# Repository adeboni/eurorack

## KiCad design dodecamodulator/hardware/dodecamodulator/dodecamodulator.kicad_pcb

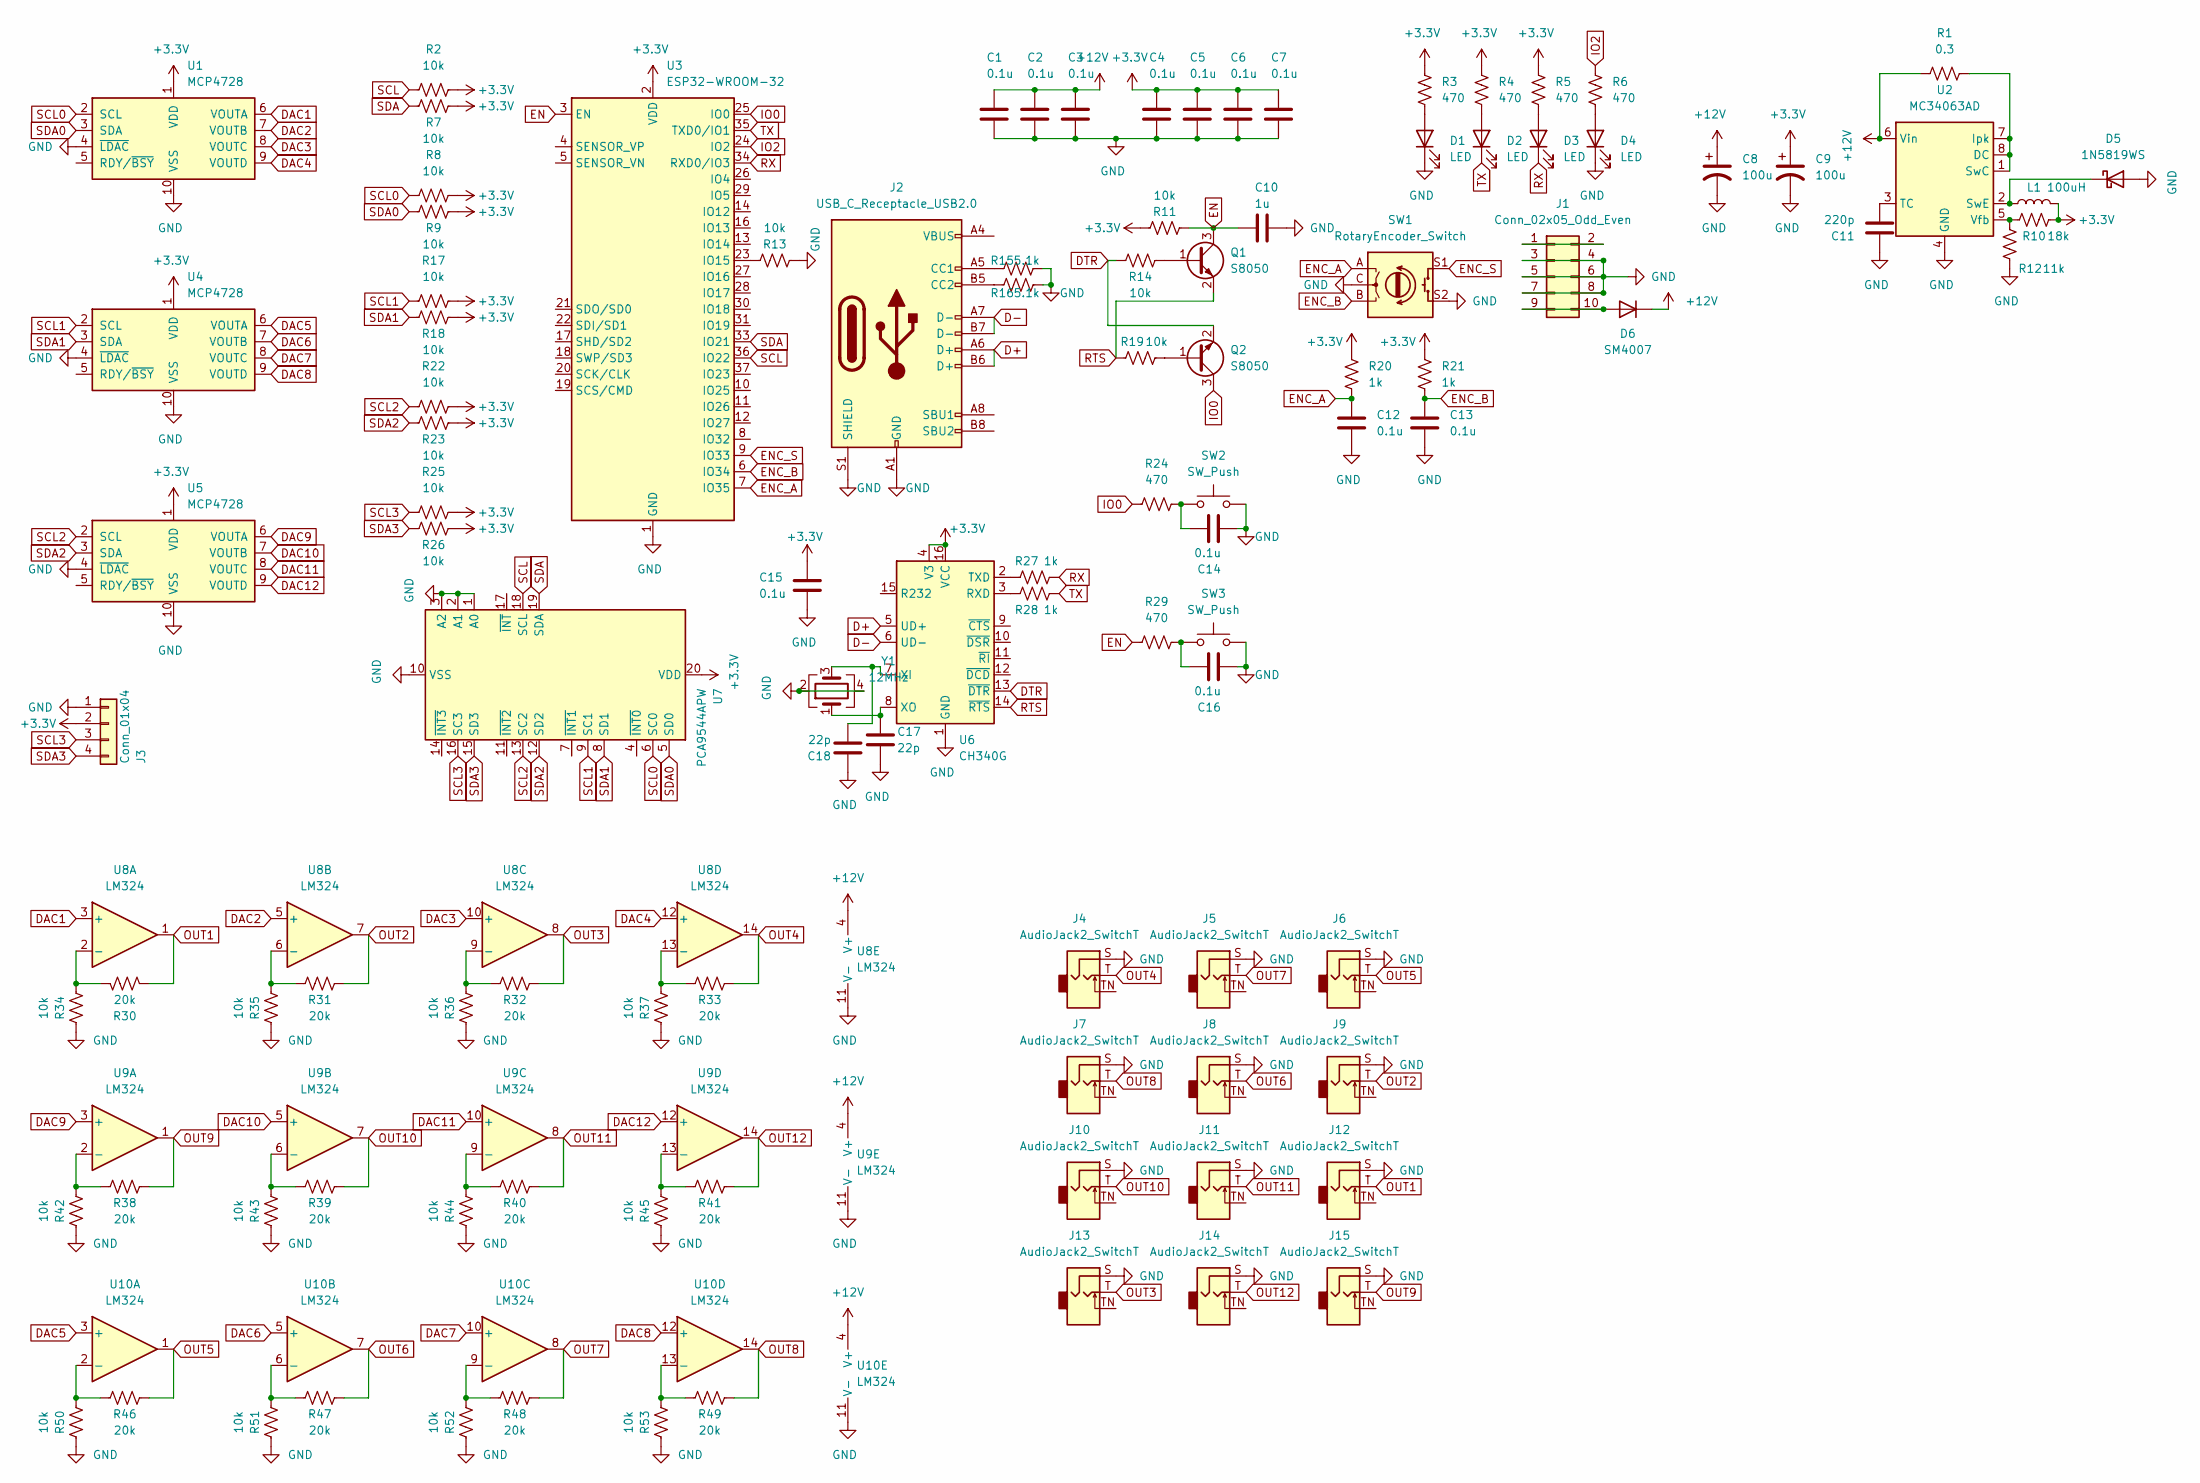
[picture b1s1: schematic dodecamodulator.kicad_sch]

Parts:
C1, C2, C3, C4, C5, C6, C7, C12, C13, C14, C15, C16: 0.1u; C_0603_1608Metric
C8, C9: 100u; CP_Elec_5x5.7
C10: 1u; C_0603_1608Metric
C11: 220p; C_0603_1608Metric
C17, C18: 22p; C_0603_1608Metric
D1, D2, D3, D4: LED; LED_0603_1608Metric
D5: 1N5819WS; D_SOD-323
D6: SM4007; D_SOD-123
J1: Conn_02x05_Odd_Even; IDC-Header_2x05_P2.54mm_Vertical
J2: USB_C_Receptacle_USB2.0; USB_C_Receptacle_Palconn_UTC16-G
J3: Conn_01x04; SSD1106
J4, J5, J6, J7, J8, J9, J10, J11, J12, J13, J14, J15: AudioJack2_SwitchT; Jack_3.5mm_QingPu_WQP-PJ398SM_Vertical_CircularHoles
L1: 100uH; L_7.3x7.3_H3.5
Q1, Q2: S8050; SOT-23
R1: 0.3; R_0603_1608Metric
R2, R7, R8, R9, R11, R13, R14, R17, R18, R19, R22, R23, R25, R26, R34, R35, R36, R37, R42, R43, R44, R45, R50, R51, R52, R53: 10k; R_0603_1608Metric
R3, R4, R5, R6, R24, R29: 470; R_0603_1608Metric
R10: 18k; R_0603_1608Metric
R12: 11k; R_0603_1608Metric
R15, R16: 5.1k; R_0603_1608Metric
R20, R21, R27, R28: 1k; R_0603_1608Metric
R30, R31, R32, R33, R38, R39, R40, R41, R46, R47, R48, R49: 20k; R_0603_1608Metric
SW1: RotaryEncoder_Switch; RotaryEncoder_Alps_EC11E-Switch_Vertical_H20mm
SW2, SW3: SW_Push; SW_SPST_TL3342
U1, U4, U5: MCP4728; MSOP-10_3x3mm_P0.5mm
U2: MC34063AD; SOIC-8_3.9x4.9mm_P1.27mm
U3: ESP32-WROOM-32
U6: CH340G; SOIC-16_3.9x9.9mm_P1.27mm
U7: PCA9544APW; TSSOP-20_4.4x6.5mm_P0.65mm
U8, U9, U10: LM324; SOIC-14_3.9x8.7mm_P1.27mm
Y1: 12MHz; Crystal_SMD_3225-4Pin_3.2x2.5mm

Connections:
+3V3: C4.1, C5.1, C6.1, C7.1, C9.1, C15.1, J3.2, L1.2, R2.2, R3.2, R4.2, R5.2, R7.2, R8.2, R9.2, R10.2, R11.2, R17.2, R18.2, R20.2, R21.2, R22.2, R23.2, R25.2, R26.2, U1.1 (VDD), U3.2 (VDD), U4.1 (VDD), U5.1 (VDD), U6.4 (V3), U6.16 (VCC), U7.20 (VDD)
+12V: C1.1, C2.1, C3.1, C8.1, D6.1 (K), R1.2, U2.6 (Vin), U8.4 (V+), U9.4 (V+), U10.4 (V+)
D+: J2.A6 (D+), J2.B6 (D+), U6.5 (UD+)
D-: J2.A7 (D-), J2.B7 (D-), U6.6 (UD-)
DAC1: U1.6 (VOUTA), U8.3 (+)
DAC2: U1.7 (VOUTB), U8.5 (+)
DAC3: U1.8 (VOUTC), U8.10 (+)
DAC4: U1.9 (VOUTD), U8.12 (+)
DAC5: U4.6 (VOUTA), U10.3 (+)
DAC6: U4.7 (VOUTB), U10.5 (+)
DAC7: U4.8 (VOUTC), U10.10 (+)
DAC8: U4.9 (VOUTD), U10.12 (+)
DAC9: U5.6 (VOUTA), U9.3 (+)
DAC10: U5.7 (VOUTB), U9.5 (+)
DAC11: U5.8 (VOUTC), U9.10 (+)
DAC12: U5.9 (VOUTD), U9.12 (+)
DTR: Q2.2 (E), R14.1, U6.13 (~DTR)
EN: C10.2, Q1.3 (C), R11.1, R29.2, U3.3 (EN)
ENC_A: C12.1, R20.1, SW1.A, U3.7 (IO35)
ENC_B: C13.1, R21.1, SW1.B, U3.6 (IO34)
ENC_S: SW1.S1, U3.9 (IO33)
GND: C1.2, C2.2, C3.2, C4.2, C5.2, C6.2, C7.2, C8.2, C9.2, C10.1, C11.1, C12.2, C13.2, C14.2, C15.2, C16.2, C17.2, C18.1, D1.1 (K), D4.1 (K), D5.2 (A), J1.3, J1.4, J1.5, J1.6, J1.7, J1.8, J2.A1 (GND), J2.A12 (GND), J2.B1 (GND), J2.B12 (GND), J2.S1 (SHIELD), J3.1, J4.S, J5.S, J6.S, J7.S, J8.S, J9.S, J10.S, J11.S, J12.S, J13.S, J14.S, J15.S, R12.2, R13.1, R15.1, R16.1, R34.2, R35.2, R36.2, R37.2, R42.2, R43.2, R44.2, R45.2, R50.2, R51.2, R52.2, R53.2, SW1.C, SW1.S2, SW2.2, SW3.2, U1.4 (~LDAC), U1.10 (VSS), U2.4 (GND), U3.1 (GND), U3.15 (GND), U3.38 (GND), U3.39 (GND), U4.4 (~LDAC), U4.10 (VSS), U5.4 (~LDAC), U5.10 (VSS), U6.1 (GND), U7.1 (A0), U7.2 (A1), U7.3 (A2), U7.10 (VSS), U8.11 (V-), U9.11 (V-), U10.11 (V-), Y1.2, Y1.4
IO0: Q2.3 (C), R24.2, U3.25 (IO0)
IO2: R6.2, U3.24 (IO2)
unnamed: C11.2, U2.3 (TC)
unnamed: C14.1, R24.1, SW2.1
unnamed: C16.1, R29.1, SW3.1
unnamed: C17.1, U6.8 (XO), Y1.1
unnamed: C18.2, U6.7 (XI), Y1.3
unnamed: D1.2 (A), R3.1
unnamed: D2.2 (A), R4.1
unnamed: D3.2 (A), R5.1
unnamed: D4.2 (A), R6.1
unnamed: D5.1 (K), L1.1, U2.2 (SwE)
unnamed: D6.2 (A), J1.9, J1.10
unnamed: J1.1, J1.2
unnamed: J2.A4 (VBUS), J2.A9 (VBUS), J2.B4 (VBUS), J2.B9 (VBUS)
unnamed: J2.A5 (CC1), R15.2
unnamed: J2.B5 (CC2), R16.2
unnamed: Q1.1 (B), R14.2
unnamed: Q2.1 (B), R19.2
unnamed: R1.1, U2.1 (SwC), U2.7 (Ipk), U2.8 (DC)
unnamed: R10.1, R12.1, U2.5 (Vfb)
unnamed: R13.2, U3.23 (IO15)
unnamed: R27.2, U6.2 (TXD)
unnamed: R28.2, U6.3 (RXD)
unnamed: R30.1, R34.1, U8.2 (-)
unnamed: R31.1, R35.1, U8.6 (-)
unnamed: R32.1, R36.1, U8.9 (-)
unnamed: R33.1, R37.1, U8.13 (-)
unnamed: R38.1, R42.1, U9.2 (-)
unnamed: R39.1, R43.1, U9.6 (-)
unnamed: R40.1, R44.1, U9.9 (-)
unnamed: R41.1, R45.1, U9.13 (-)
unnamed: R46.1, R50.1, U10.2 (-)
unnamed: R47.1, R51.1, U10.6 (-)
unnamed: R48.1, R52.1, U10.9 (-)
unnamed: R49.1, R53.1, U10.13 (-)
OUT1: J12.T, R30.2, U8.1
OUT2: J9.T, R31.2, U8.7
OUT3: J13.T, R32.2, U8.8
OUT4: J4.T, R33.2, U8.14
OUT5: J6.T, R46.2, U10.1
OUT6: J8.T, R47.2, U10.7
OUT7: J5.T, R48.2, U10.8
OUT8: J7.T, R49.2, U10.14
OUT9: J15.T, R38.2, U9.1
OUT10: J10.T, R39.2, U9.7
OUT11: J11.T, R40.2, U9.8
OUT12: J14.T, R41.2, U9.14
RTS: Q1.2 (E), R19.1, U6.14 (~RTS)
RX: D3.1 (K), R27.1, U3.34 (RXD0/IO3)
SCL: R2.1, U3.36 (IO22), U7.18 (SCL)
SCL0: R8.1, U1.2 (SCL), U7.6 (SC0)
SCL1: R17.1, U4.2 (SCL), U7.9 (SC1)
SCL2: R22.1, U5.2 (SCL), U7.13 (SC2)
SCL3: J3.3, R25.1, U7.16 (SC3)
SDA: R7.1, U3.33 (IO21), U7.19 (SDA)
SDA0: R9.1, U1.3 (SDA), U7.5 (SD0)
SDA1: R18.1, U4.3 (SDA), U7.8 (SD1)
SDA2: R23.1, U5.3 (SDA), U7.12 (SD2)
SDA3: J3.4, R26.1, U7.15 (SD3)
TX: D2.1 (K), R28.1, U3.35 (TXD0/IO1)

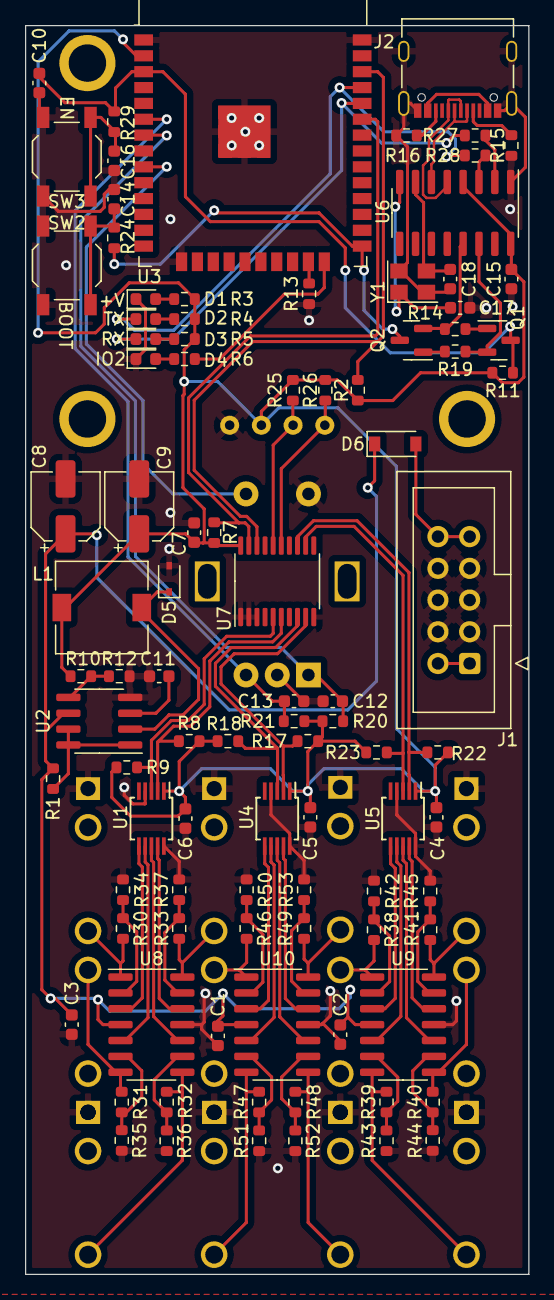
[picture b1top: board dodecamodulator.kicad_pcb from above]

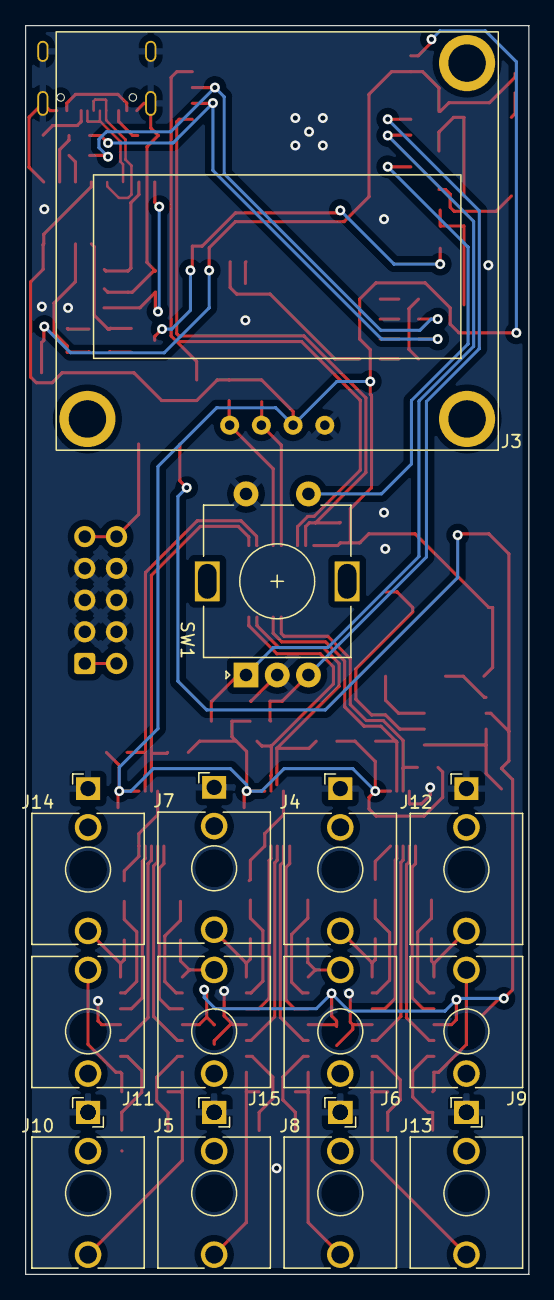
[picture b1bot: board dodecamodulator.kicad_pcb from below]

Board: 2 copper layers, 40.3 x 100.0 mm, 109 parts (14 on the bottom side), 83 nets.

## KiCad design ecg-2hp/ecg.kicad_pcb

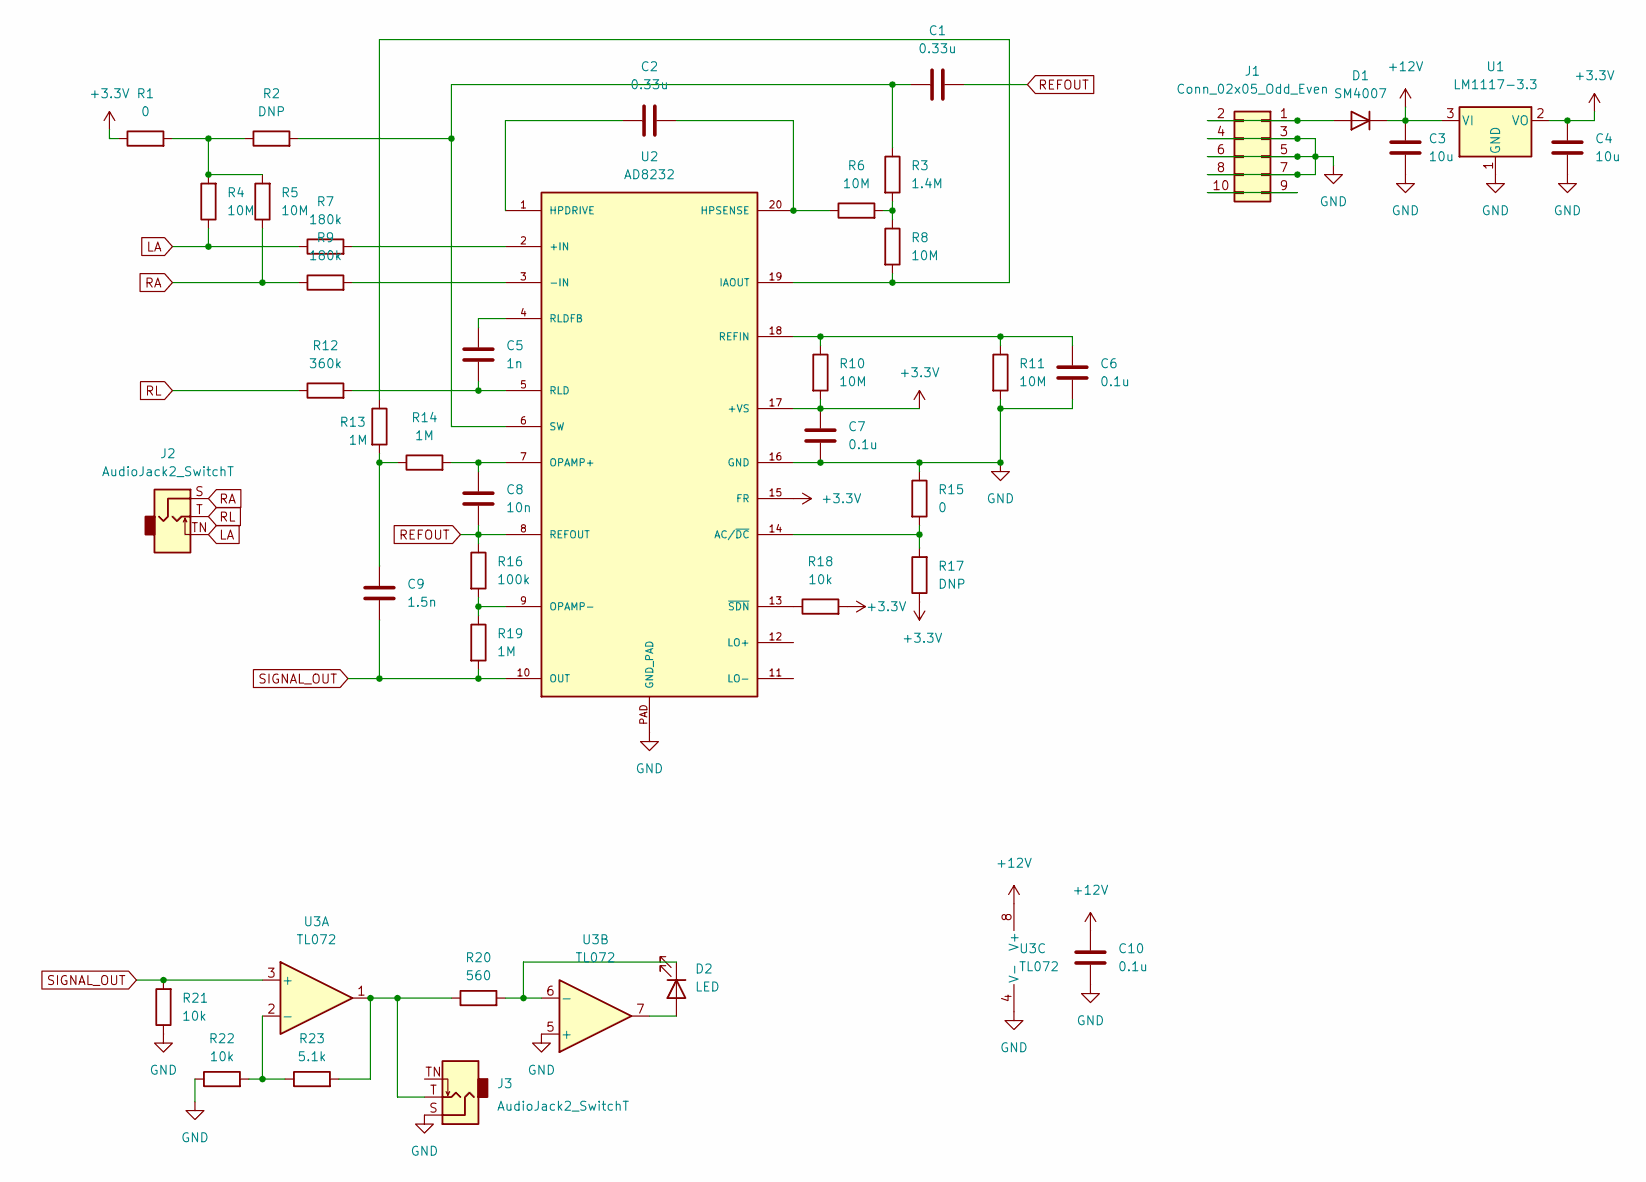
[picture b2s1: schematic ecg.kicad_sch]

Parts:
C1, C2: 0.33u; C_0603_1608Metric
C3, C4: 10u; C_0603_1608Metric
C5: 1n; C_0603_1608Metric
C6, C7, C10: 0.1u; C_0603_1608Metric
C8: 10n; C_0603_1608Metric
C9: 1.5n; C_0603_1608Metric
D1: SM4007; D_SOD-123
D2: LED; LED_D3.0mm_FlatTop
J1: Conn_02x05_Odd_Even; Pins_2x05_2.54mm_TH_Europower
J2, J3: AudioJack2_SwitchT; Jack_3.5mm_QingPu_WQP-PJ398SM_Vertical_CircularHoles
R1, R15: 0; R_0603_1608Metric
R2, R17: DNP; R_0603_1608Metric
R3: 1.4M; R_0603_1608Metric
R4, R5, R6, R8, R10, R11: 10M; R_0603_1608Metric
R7, R9: 180k; R_0603_1608Metric
R12: 360k; R_0603_1608Metric
R13, R14, R19: 1M; R_0603_1608Metric
R16: 100k; R_0603_1608Metric
R18, R21, R22: 10k; R_0603_1608Metric
R20: 560; R_0603_1608Metric
R23: 5.1k; R_0603_1608Metric
U1: LM1117-3.3; SOT-223-3_TabPin2
U2: AD8232; LFCSP_20
U3: TL072; SOIC-8_3.9x4.9mm_P1.27mm

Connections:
+3V3: C4.2, C7.2, R1.1, R10.2, R17.1, R18.2, U1.2 (VO), U2.15 (FR), U2.17 (+VS)
+12V: C3.2, C10.2, D1.1 (K), U1.3 (VI), U3.8 (V+)
GND: C3.1, C4.1, C6.1, C7.1, C10.1, J1.3, J1.4, J1.5, J1.6, J1.7, J1.8, J3.S, R11.2, R15.1, R21.1, R22.1, U1.1 (GND), U2.16 (GND), U2.PAD (GND_PAD), U3.4 (V-), U3.5 (+)
LA: J2.TN, R4.1, R7.1
unnamed: C1.2, R2.2, R3.1, U2.6 (SW)
unnamed: C2.1, R6.1, U2.20 (HPSENSE)
unnamed: C2.2, U2.1 (HPDRIVE)
unnamed: C5.1, R12.2, U2.5 (RLD)
unnamed: C5.2, U2.4 (RLDFB)
unnamed: C6.2, R10.1, R11.1, U2.18 (REFIN)
unnamed: C8.2, R14.2, U2.7 (OPAMP+)
unnamed: C9.2, R13.2, R14.1
unnamed: D1.2 (A), J1.1, J1.2
unnamed: D2.1 (K), R20.2, U3.6 (-)
unnamed: D2.2 (A), U3.7
unnamed: J1.9, J1.10
unnamed: J3.T, R20.1, R23.2, U3.1
unnamed: R1.2, R2.1, R4.2, R5.2
unnamed: R3.2, R6.2, R8.1
unnamed: R7.2, U2.2 (+IN)
unnamed: R9.2, U2.3 (-IN)
unnamed: R8.2, R13.1, U2.19 (IAOUT)
unnamed: R15.2, R17.2, U2.14 (AC/~DC)
unnamed: R16.2, R19.1, U2.9 (OPAMP-)
unnamed: R18.1, U2.13 (~SDN)
unnamed: R22.2, R23.1, U3.2 (-)
RA: J2.S, R5.1, R9.1
REFOUT: C1.1, C8.1, R16.1, U2.8 (REFOUT)
RL: J2.T, R12.1
SIGNAL_OUT: C9.1, R19.2, R21.2, U2.10 (OUT), U3.3 (+)

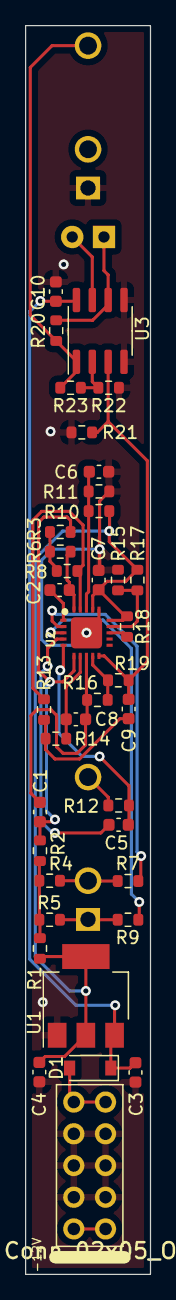
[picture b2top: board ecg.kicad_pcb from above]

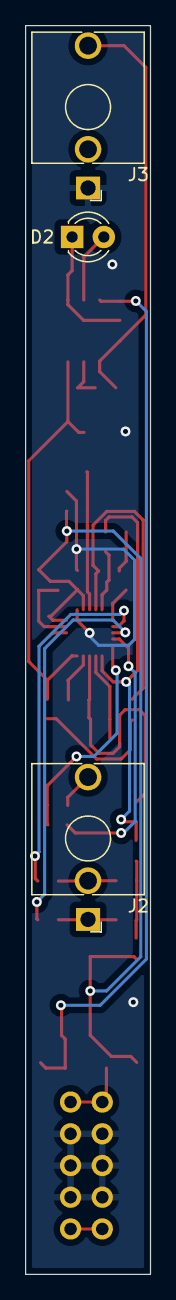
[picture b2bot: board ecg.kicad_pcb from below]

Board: 2 copper layers, 10.0 x 100.0 mm, 41 parts (3 on the bottom side), 30 nets.

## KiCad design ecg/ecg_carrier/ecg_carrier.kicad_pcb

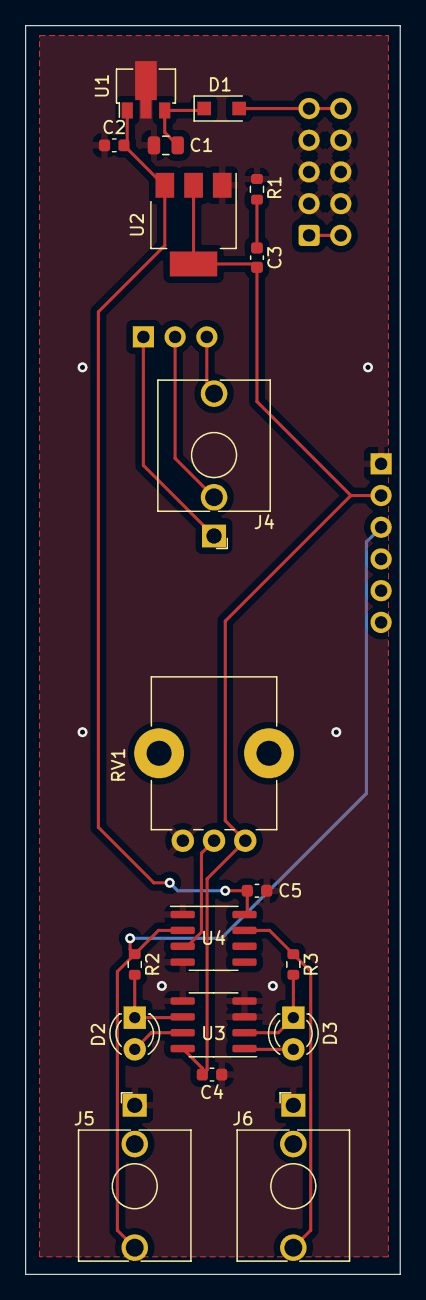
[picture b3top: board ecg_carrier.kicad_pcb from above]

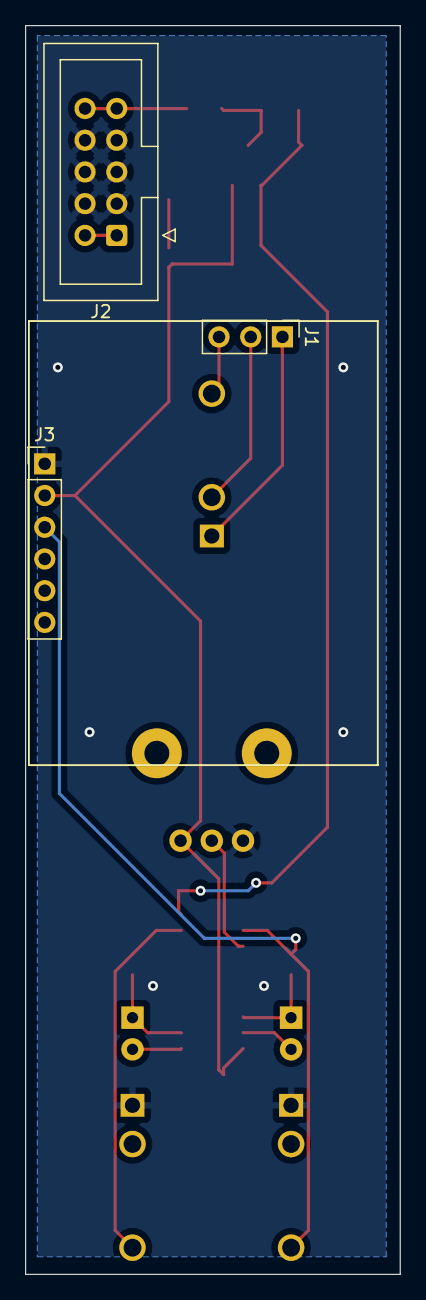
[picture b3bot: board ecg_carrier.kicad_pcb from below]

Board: 2 copper layers, 30.0 x 100.0 mm, 22 parts (3 on the bottom side), 17 nets.

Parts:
C1: 22u; C_0805_2012Metric
C2, C3: 10u; C_0603_1608Metric
C4, C5: 0.1u; C_0603_1608Metric
D1: 1N5819; D_SOD-123F
D2, D3: LED; LED_D3.0mm_FlatTop
J1: Conn_01x03; PinHeader_1x03_P2.54mm_Vertical
J2: Conn_02x05_Odd_Even; IDC-Header_2x05_P2.54mm_Vertical
J3: Conn_01x06; PinHeader_1x06_P2.54mm_Vertical
J4, J5, J6: AudioJack2_SwitchT; Jack_3.5mm_QingPu_WQP-PJ398SM_Vertical_CircularHoles
R1: 10; R_0603_1608Metric
R2, R3: 47; R_0603_1608Metric
RV1: R_Potentiometer; Potentiometer_Alps_RK09K_Single_Vertical
U1: L78L05_SOT89; SOT-89-3
U2: LM1117-3.3; SOT-223-3_TabPin2
U3: TL072; SOIC-8_3.9x4.9mm_P1.27mm
U4: LM311; SOIC-8_3.9x4.9mm_P1.27mm

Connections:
+3V3: C3.2, C4.2, J3.2, RV1.1, U2.2 (VO), U3.8 (V+)
+5V: C2.2, C5.2, U1.1 (OUT), U2.3 (VI), U4.8 (V+)
GATE_OUT: J6.T, R3.1, U4.7
GND: C1.1, C2.1, C4.1, C5.1, J2.3, J2.4, J2.5, J2.6, J2.7, J2.8, J3.1, J5.S, J6.S, R1.2, RV1.3, U1.2 (GND), U2.1 (GND), U3.3 (+), U3.4 (V-), U3.5 (+), U4.1 (GND), U4.4 (V-)
LA: J1.2, J4.TN
unnamed: C1.2, D1.1 (K), U1.3 (IN)
unnamed: C3.1, R1.1
unnamed: D1.2 (A), J2.9, J2.10
unnamed: D2.1 (K), R2.2, U3.6 (-)
unnamed: D2.2 (A), U3.7
unnamed: D3.1 (K), R3.2, U3.2 (-)
unnamed: D3.2 (A), U3.1
unnamed: J2.1, J2.2
unnamed: RV1.2, U4.3 (-)
RA: J1.1, J4.S
RL: J1.3, J4.T
SIGNAL_OUT: J3.3, J5.T, R2.1, U4.2 (+)
